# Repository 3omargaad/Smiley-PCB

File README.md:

# Smiley-PCB
This is a simple circuit the starts of frowny :(
but when you push a button, it smiles :)

Electronic Hardware Needed:
- x9 White LEDs (5mm)
- x9 330Ω Resistors (THT)
- x2 10kΩ Resistors (THT)
- x1 1kΩ Resistor (THT)
- x2 Push Buttons (THT)
- x1 555 Timer IC (NE555P)
- x1 22nF Non-Polarised Capacitor (THT) (Optional)
- x2 NPN Transistors (2N2222 A331)
- x2 AA Batteries (1.2-1.5V)
- x1 AA Battery Holder

No Code Required.

🛠️ Designed with KiCAD v9.0.0

Download the [gerber.zip](https://github.com/3omargaad/Smiley-PCB/blob/main/gerber.zip) file and order from a manufacturer like JLCPBC or PCBWay to get the PCB itself.

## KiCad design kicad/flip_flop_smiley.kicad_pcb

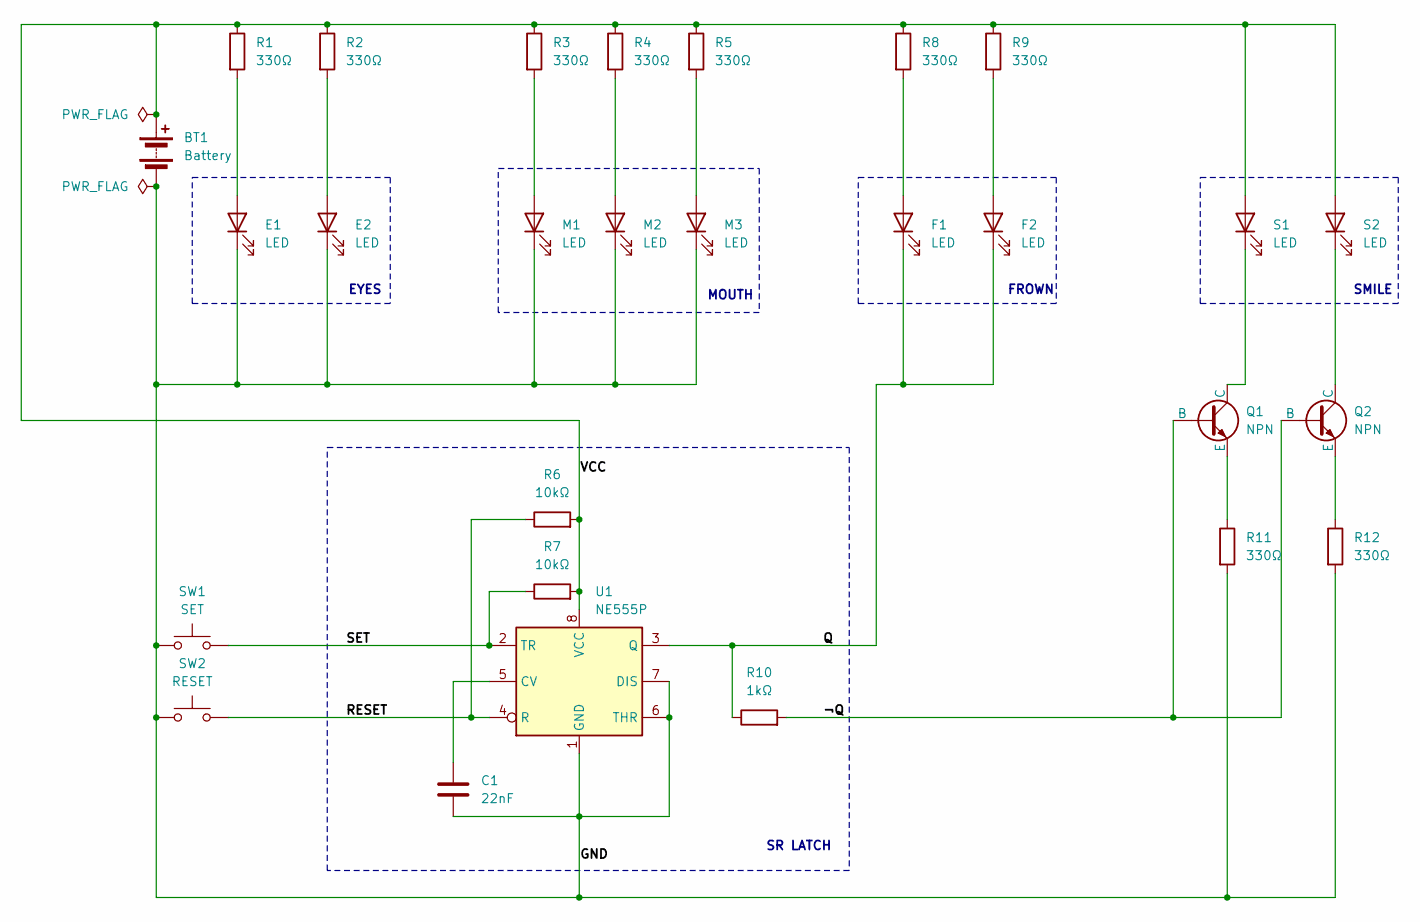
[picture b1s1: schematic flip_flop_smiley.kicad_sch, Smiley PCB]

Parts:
BT1: Battery; BatteryHolder_Keystone_2462_2xAA
C1: 22nF; C_Rect_L4.0mm_W2.5mm_P2.50mm
E1, E2: LED; LED_D5.0mm
F1, F2: LED; LED_D5.0mm
M1, M2, M3: LED; LED_D5.0mm
Q1, Q2: NPN; Transistor_2N2222_A331
R1, R2, R3, R4, R5, R8, R9, R11, R12: 330Ω; R_Axial_DIN0204_L3.6mm_D1.6mm_P5.08mm_Horizontal
R6, R7: 10kΩ; R_Axial_DIN0204_L3.6mm_D1.6mm_P5.08mm_Horizontal
R10: 1kΩ; R_Axial_DIN0204_L3.6mm_D1.6mm_P5.08mm_Horizontal
S1, S2: LED; LED_D5.0mm
SW1: SET; SW_PUSH_6mm
SW2: RESET; SW_PUSH_6mm
U1: NE555P; DIP-8_W7.62mm

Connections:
/GND: BT1.2 (-), C1.2, E1.1 (K), E2.1 (K), M1.1 (K), M2.1 (K), M3.1 (K), R11.2, R12.2, SW1.1, SW2.1, U1.1 (GND), U1.6 (THR), U1.7 (DIS)
/Q: F1.1 (K), F2.1 (K), R10.1, U1.3 (Q)
/RESET: R6.1, SW2.2, U1.4 (R)
/SET: R7.1, SW1.2, U1.2 (TR)
/VCC: BT1.1 (+), R1.1, R2.1, R3.1, R4.1, R5.1, R6.2, R7.2, R8.1, R9.1, S1.2 (A), S2.2 (A), U1.8 (VCC)
/¬Q: Q1.2 (B), Q2.2 (B), R10.2
unnamed: E1.2 (A), R1.2
unnamed: E2.2 (A), R2.2
unnamed: F1.2 (A), R8.2
unnamed: F2.2 (A), R9.2
unnamed: M1.2 (A), R3.2
unnamed: M2.2 (A), R4.2
unnamed: M3.2 (A), R5.2
unnamed: Q1.1 (C), S1.1 (K)
unnamed: Q1.3 (E), R11.1
unnamed: Q2.1 (C), S2.1 (K)
unnamed: Q2.3 (E), R12.1
unnamed: C1.1, U1.5 (CV)

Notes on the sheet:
EYES
SMILE
FROWN
SR LATCH
MOUTH

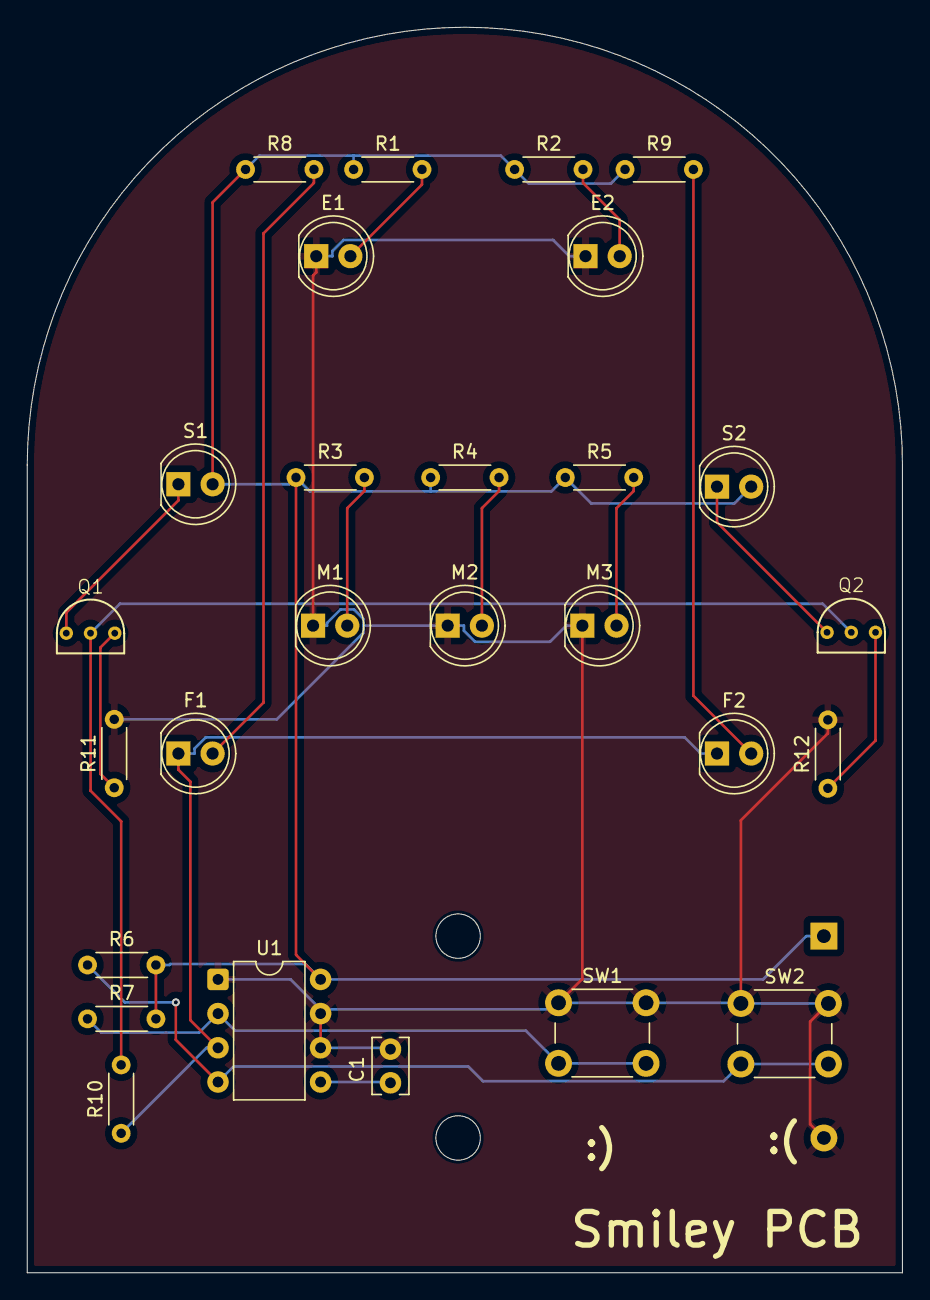
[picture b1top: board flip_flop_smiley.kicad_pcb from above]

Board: 2 copper layers, 65.0 x 92.5 mm, 28 parts (1 on the bottom side), 18 nets.

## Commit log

2025-04-09 Added Schematic
2025-04-09 Rename image_2025-04-09_182103519.png to schematic.png
2025-04-09 Icon Added
2025-04-14 Added 3D Model (FRONT)
2025-04-14 Rename image_2025-04-14_193729724.png to 3D_Model_FRONT.png
2025-04-14 Added 3D Model (Back)
2025-04-14 Rename image_2025-04-14_194015767.png to 3D_Model_BACK.png
2025-04-14 Create images
2025-04-14 Added gerber.zip
2025-04-14 Organised Images
2025-04-15 Removed Icon
2025-04-15 Edited README.md
2025-04-15 Uploaded KiCAD files
2025-04-15 Added Transistor THT Footprint
2025-04-15 Organised Files
2025-04-15 Added PCB Design
2025-04-15 Rename image_2025-04-15_103600045.png to pcb_design.png
